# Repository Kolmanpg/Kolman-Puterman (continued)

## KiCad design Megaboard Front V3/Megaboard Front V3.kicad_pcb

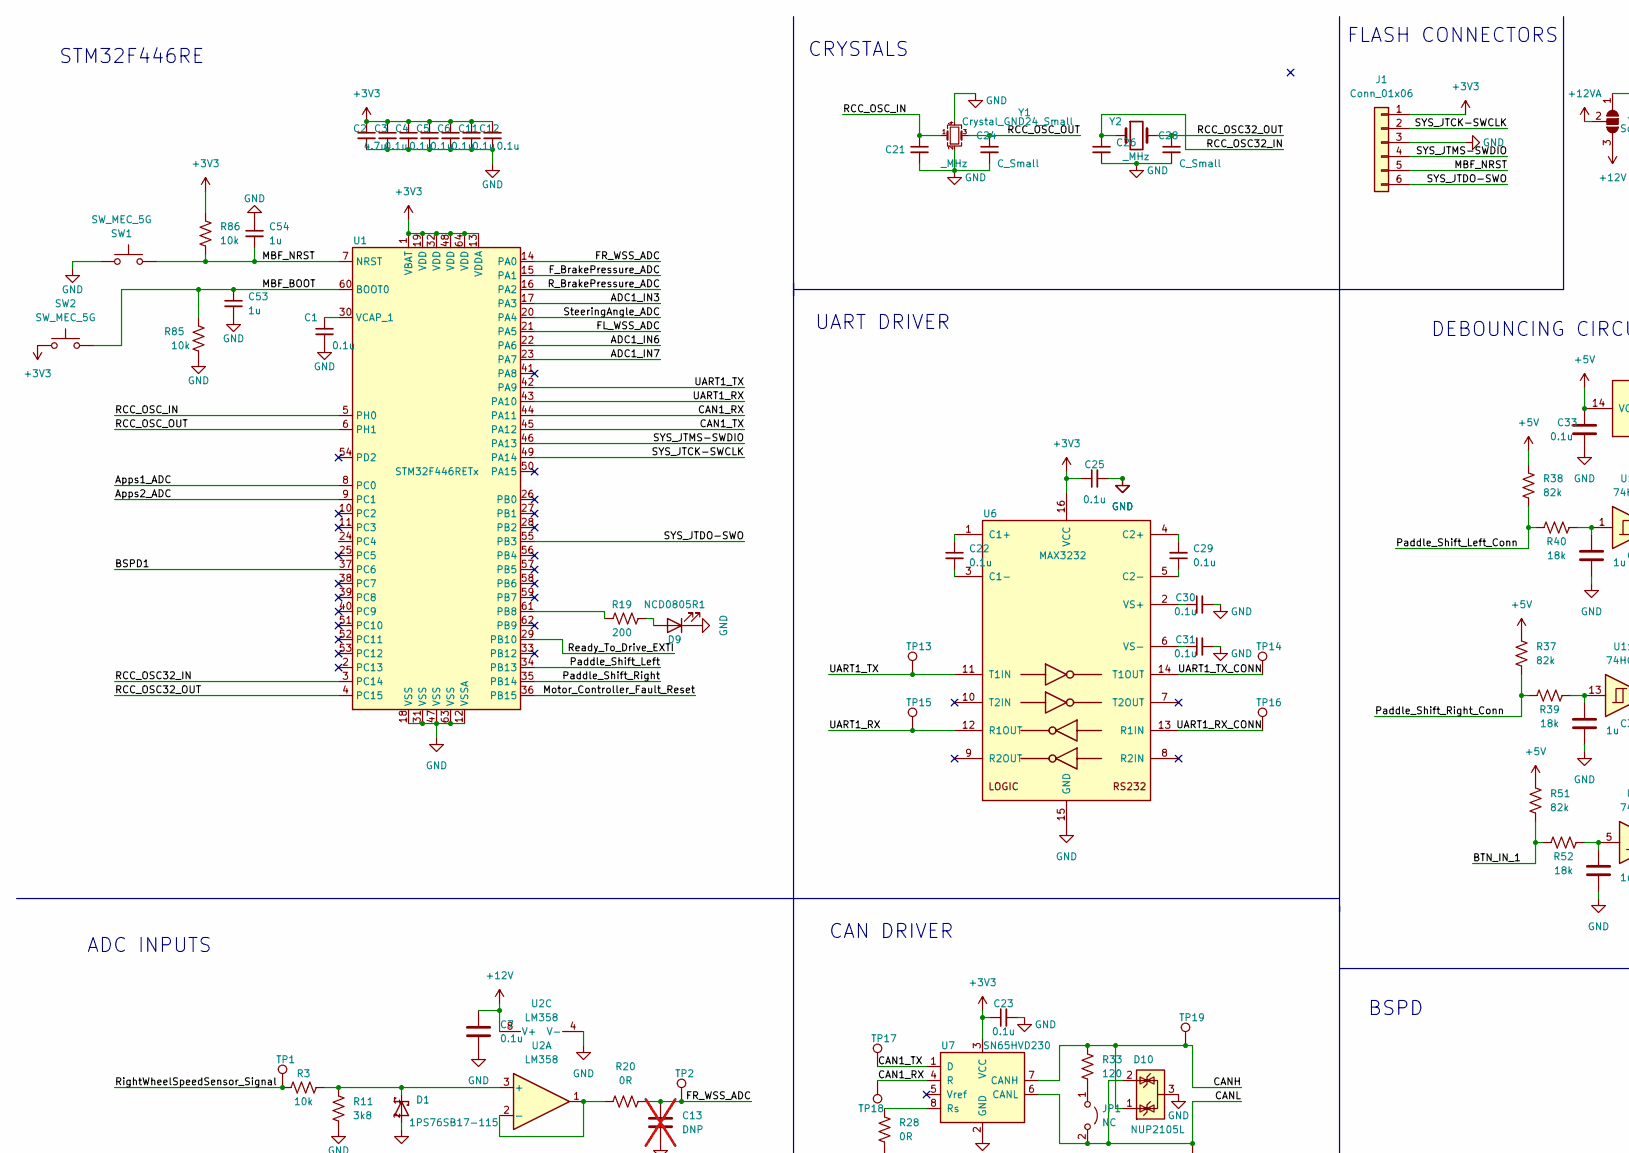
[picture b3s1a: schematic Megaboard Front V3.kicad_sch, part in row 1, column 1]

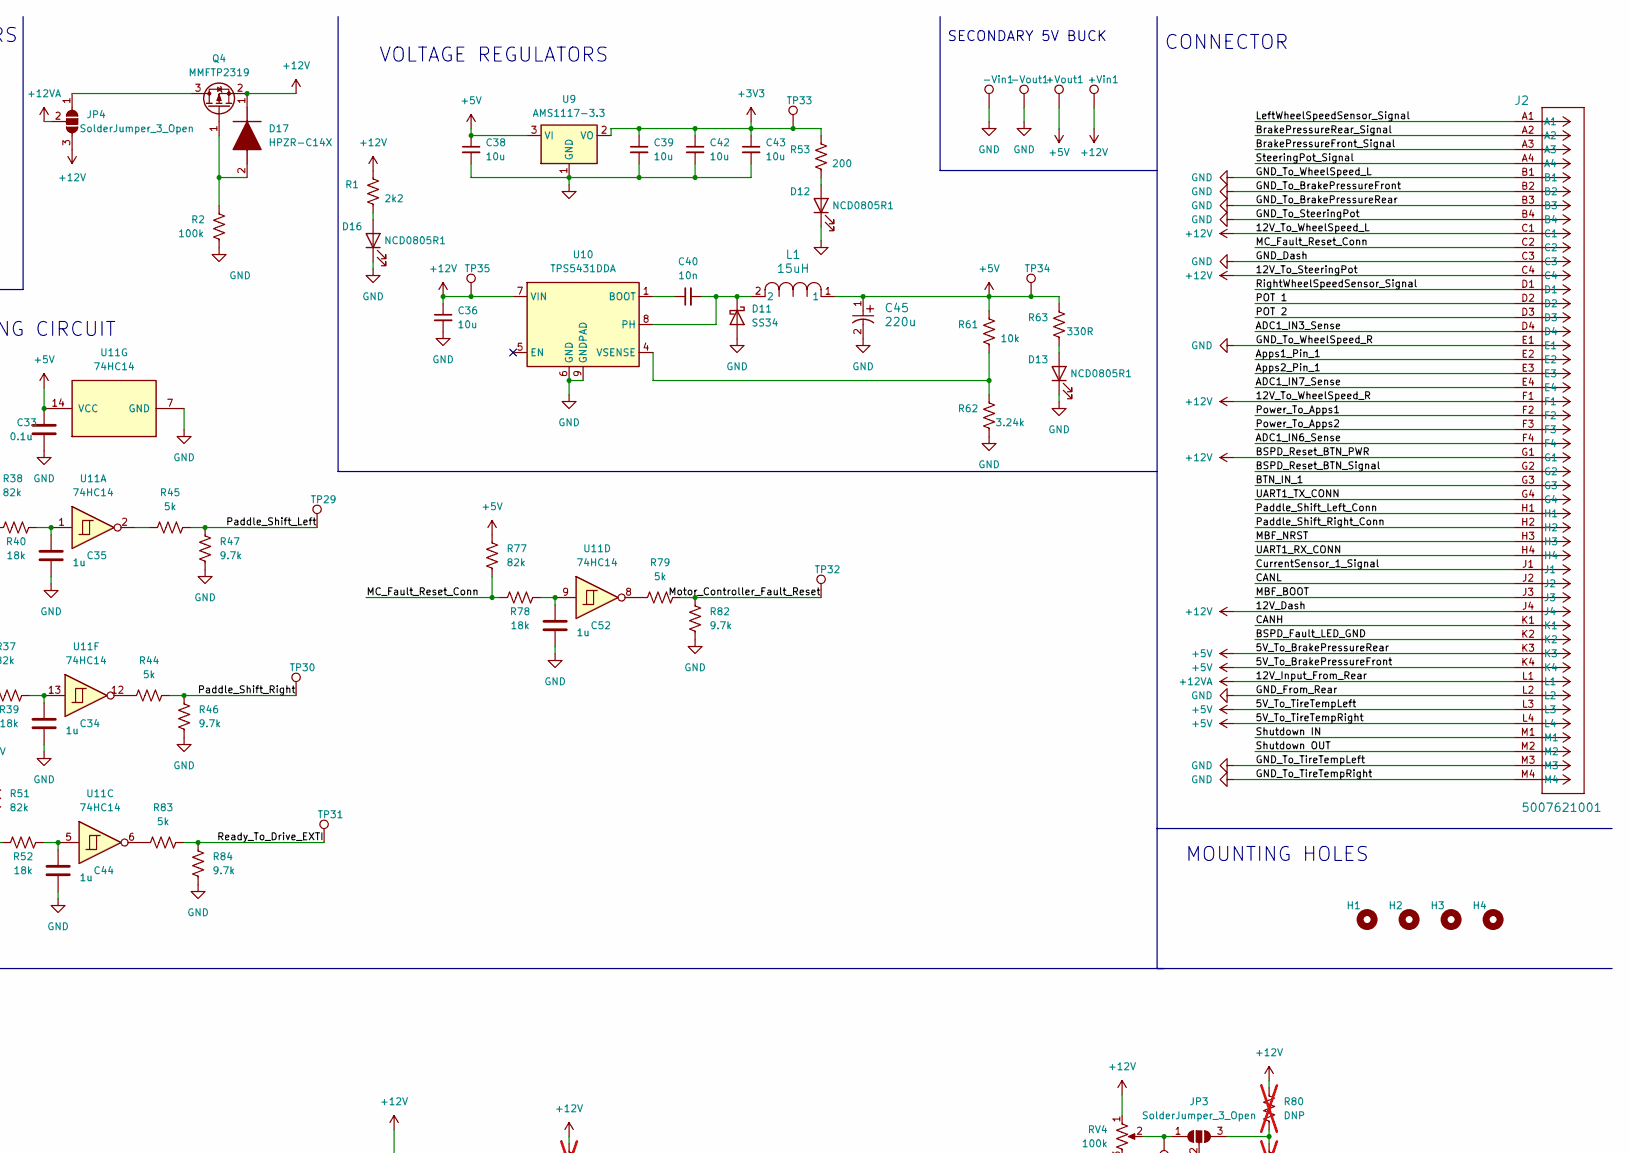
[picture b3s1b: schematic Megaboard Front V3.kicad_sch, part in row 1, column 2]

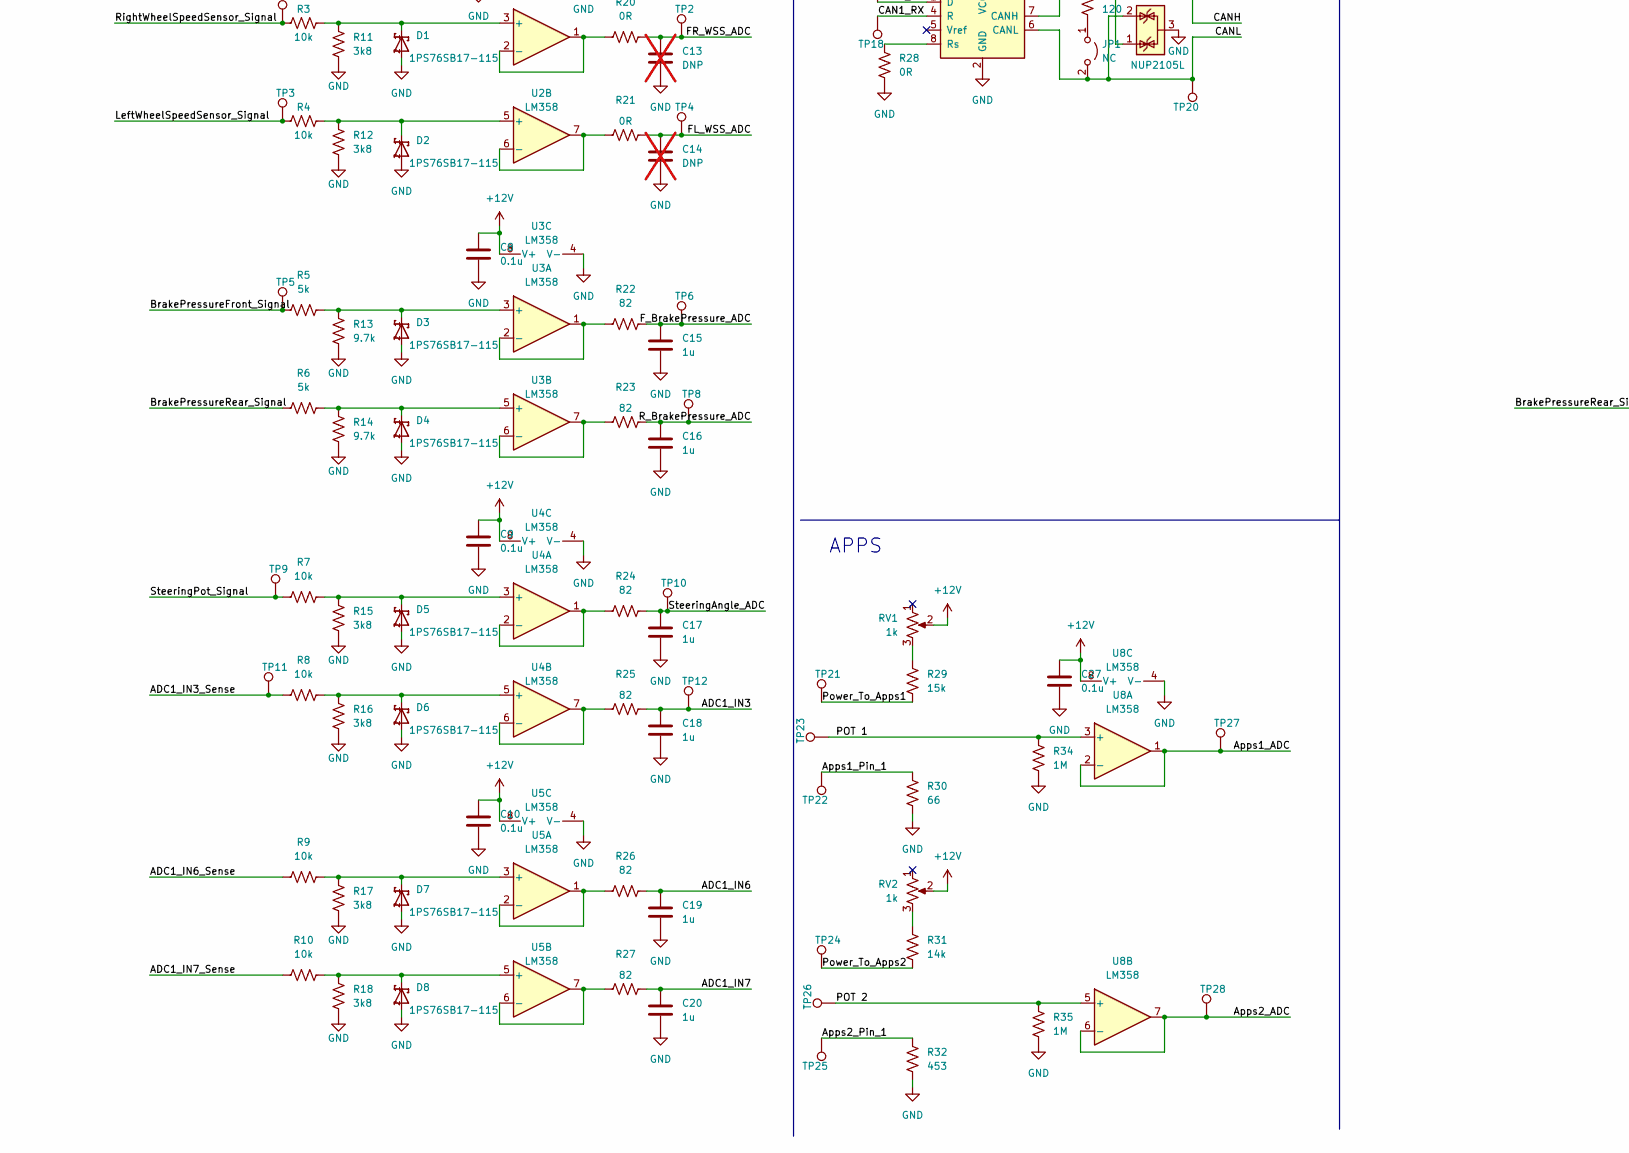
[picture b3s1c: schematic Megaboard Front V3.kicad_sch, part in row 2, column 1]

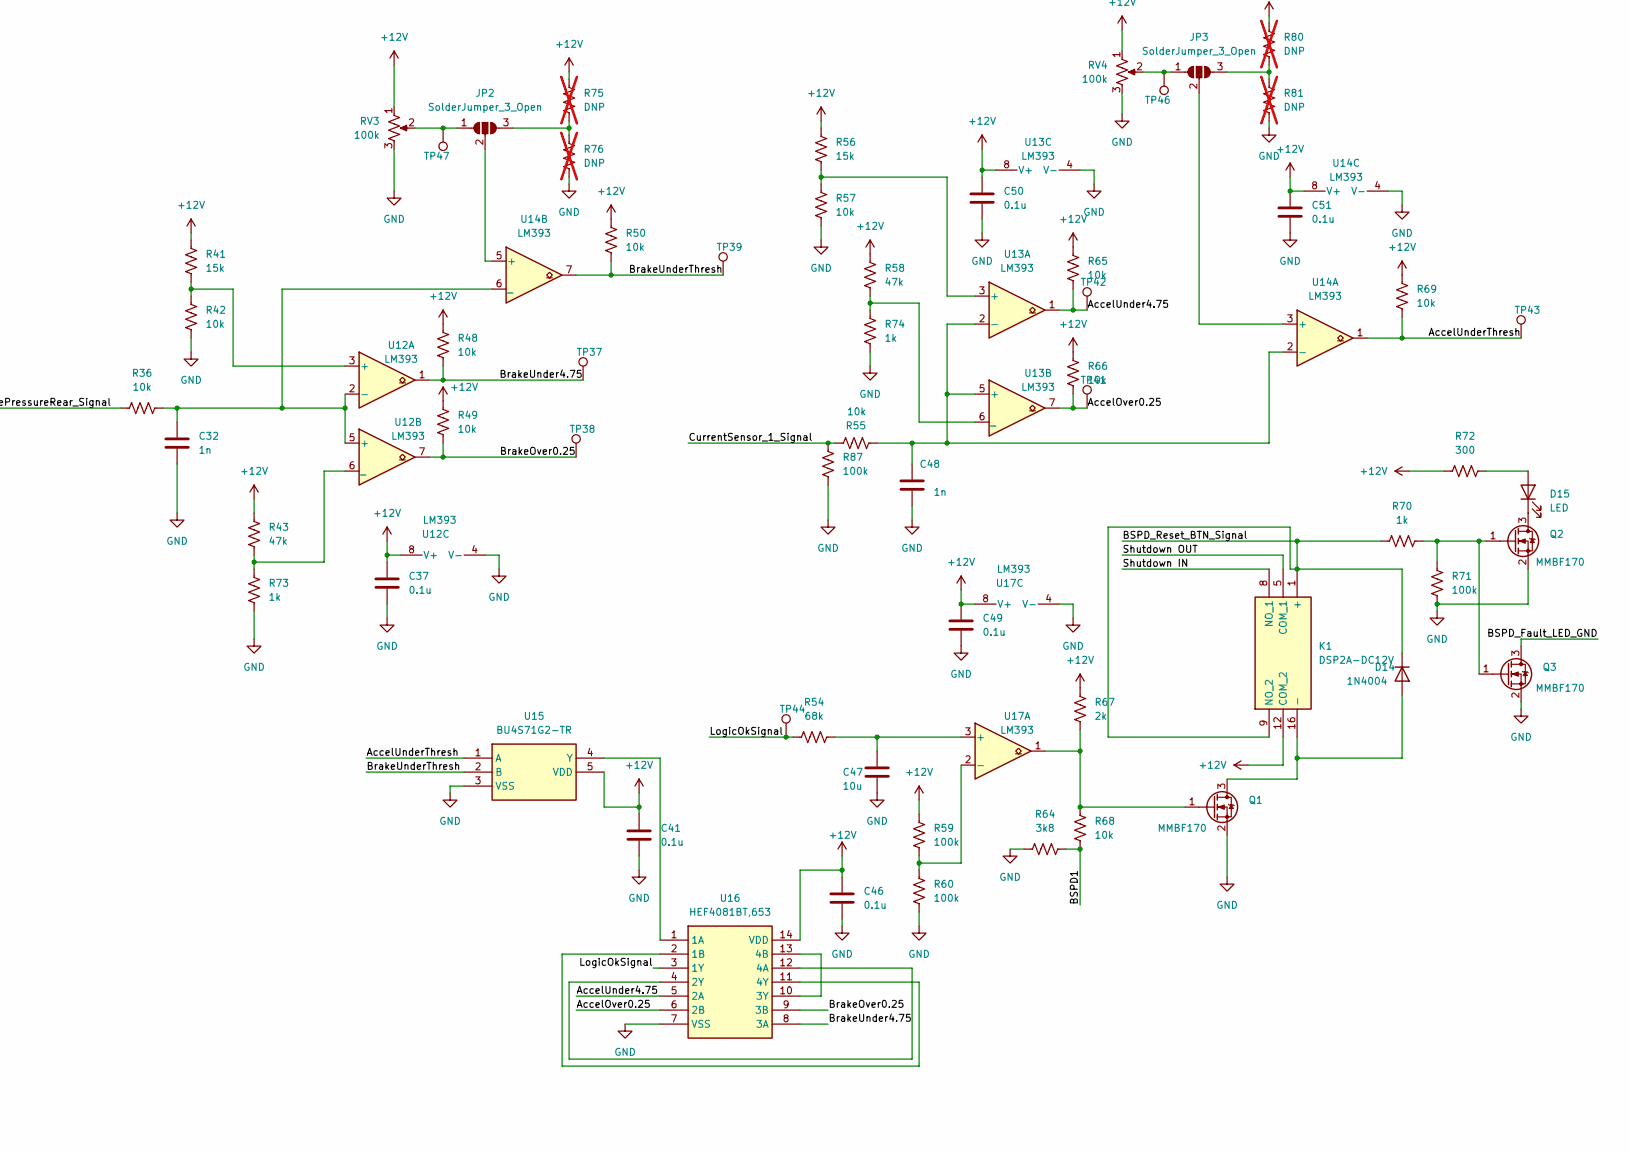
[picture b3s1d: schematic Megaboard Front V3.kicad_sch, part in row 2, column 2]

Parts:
+Vin1: TestPoint_Pad_D1.0mm; MPN DNP; JLCPCB Part # DNP
+Vout1: TestPoint_Pad_D1.0mm; MPN DNP; JLCPCB Part # DNP
-Vin1: TestPoint_Pad_D1.0mm; MPN DNP; JLCPCB Part # DNP
-Vout1: TestPoint_Pad_D1.0mm; MPN DNP; JLCPCB Part # DNP
C1, C3, C4, C5, C6, C11, C12, C22, C23, C25, C29, C30, C31: 0.1u; C_0805_2012Metric_Pad1.18x1.45mm_HandSolder; JLCPCB Part # C49678
C2: 4.7u; C_0805_2012Metric_Pad1.18x1.45mm_HandSolder; JLCPCB Part # C1779
C7, C8, C9, C10, C27, C33: 0.1u; C_0805_2012Metric_Pad1.18x1.45mm_HandSolder; MPN C28233; JLCPCB Part # C49678
C13, C14: DNP; C_0805_2012Metric_Pad1.18x1.45mm_HandSolder; MPN C28323; JLCPCB Part # DNP; not fitted
C15, C16, C17, C18, C19, C20, C34, C35, C44, C52: 1u; C_0805_2012Metric_Pad1.18x1.45mm_HandSolder; MPN C28323; JLCPCB Part # C28323
C21, C26: _MHz; C_0805_2012Metric_Pad1.18x1.45mm_HandSolder; JLCPCB Part # DNP
C24, C28: C_Small; C_0805_2012Metric_Pad1.18x1.45mm_HandSolder; JLCPCB Part # DNP
C32, C48: 1n; C_0805_2012Metric_Pad1.18x1.45mm_HandSolder; MPN C35216; JLCPCB Part # C46653
C36: 10u; C_0805_2012Metric_Pad1.18x1.45mm_HandSolder; MPN C15850; JLCPCB Part # C15850
C37, C41, C46, C49, C50, C51: 0.1u; C_0805_2012Metric_Pad1.18x1.45mm_HandSolder; MPN C35216; JLCPCB Part # C49678
C38, C39, C42, C43: 10u; CP_EIA-3216-18_Kemet-A; MPN C15850; JLCPCB Part # C7171
C40: 10n; C_0805_2012Metric_Pad1.18x1.45mm_HandSolder; MPN C15850; JLCPCB Part # C1710
C45: 220u; PCAP_TPB_D4_PAN; MPN 10TPB220M; JLCPCB Part # C242173
C47: 10u; C_0805_2012Metric_Pad1.18x1.45mm_HandSolder; MPN C13585; JLCPCB Part # C15850
C53, C54: 1u; C_0805_2012Metric_Pad1.18x1.45mm_HandSolder; MPN C15850; JLCPCB Part # C28323
D1, D2, D3, D4, D5, D6, D7, D8: 1PS76SB17-115; SOD323_F_; JLCPCB Part # C551398
D9, D12, D13, D16: NCD0805R1; LED_0805_2012Metric_Pad1.15x1.40mm_HandSolder; MPN C84256; JLCPCB Part # C84256
D10: NUP2105L; SOT-23; JLCPCB Part # C2890118
D11: SS34; D_SMA; JLCPCB Part # C8678
D14: 1N4004; D_SMA_Handsoldering; MPN C95872; JLCPCB Part # C727080
D15: LED; LED_0805_2012Metric_Pad1.15x1.40mm_HandSolder; MPN C2297; JLCPCB Part # C2297
D17: HPZR-C14X; HPZRC14X; Mouser Part Number 771-HPZR-C14X
H1, H2, H3, H4: MountingHole; MountingHole_3.2mm_M3; JLCPCB Part # DNP
J1: Conn_01x06; PinHeader_2x03_P2.54mm_Vertical; JLCPCB Part # DNP
J2: 5007621001; CONN_500762-1001_MOL; JLCPCB Part # DNP
JP1: NC; SolderJumper-2_P1.3mm_Open_RoundedPad1.0x1.5mm; JLCPCB Part # DNP
JP2, JP3, JP4: SolderJumper_3_Open; SolderJumper-3_P1.3mm_Open_RoundedPad1.0x1.5mm
K1: DSP2A-DC12V; RELAY_DSP2A_PAN; Mouser Part Number 769-DSP2A-DC12V
L1: 15uH; IND_CDRH104_SUM; MPN CDRH104RNP-150NC; JLCPCB Part # C225048
Q1, Q2, Q3: MMBF170; SOT-23; MPN C130879; JLCPCB Part # C151058
Q4: MMFTP2319; SOT-23; JLCPCB Part # DNP
R1: 2k2; R_0805_2012Metric_Pad1.20x1.40mm_HandSolder; MPN C17630; JLCPCB Part # C17520
R2: 100k; R_0805_2012Metric_Pad1.20x1.40mm_HandSolder; MPN C17630; JLCPCB Part # C149504
R3, R4, R7, R8, R9, R10: 10k; R_0805_2012Metric_Pad1.20x1.40mm_HandSolder; MPN C23255; JLCPCB Part # C17414
R5, R6, R44, R45, R79, R83: 5k; R_0805_2012Metric_Pad1.20x1.40mm_HandSolder; MPN C23255; JLCPCB Part # C2828700
R11, R12, R15, R16, R17, R18, R64: 3k8; R_0805_2012Metric_Pad1.20x1.40mm_HandSolder; MPN C23255; JLCPCB Part # C228799
R13, R14, R46, R47, R82, R84: 9.7k; R_0805_2012Metric_Pad1.20x1.40mm_HandSolder; MPN C23255; JLCPCB Part # C374689
R19: 200; R_0805_2012Metric_Pad1.20x1.40mm_HandSolder; MPN C706418; JLCPCB Part # C17540
R20, R21: 0R; R_0805_2012Metric_Pad1.20x1.40mm_HandSolder; MPN C23255; JLCPCB Part # C17477
R22, R23, R24, R25, R26, R27: 82; R_0805_2012Metric_Pad1.20x1.40mm_HandSolder; MPN C23255; JLCPCB Part # C17841
R28: 0R; R_0805_2012Metric_Pad1.20x1.40mm_HandSolder; MPN C21189; JLCPCB Part # C17477
R29: 15k; R_0805_2012Metric_Pad1.20x1.40mm_HandSolder; JLCPCB Part # C17475
R30: 66; R_0805_2012Metric_Pad1.20x1.40mm_HandSolder
R31: 14k; R_0805_2012Metric_Pad1.20x1.40mm_HandSolder; JLCPCB Part # C17464
R32: 453; R_0805_2012Metric_Pad1.20x1.40mm_HandSolder
R33: 120; R_0805_2012Metric_Pad1.20x1.40mm_HandSolder; MPN C22787; JLCPCB Part # C17437
R34, R35: 1M; R_0805_2012Metric_Pad1.20x1.40mm_HandSolder; JLCPCB Part # C17514
R36, R48, R49, R50, R55, R65, R66, R69: 10k; R_0805_2012Metric_Pad1.20x1.40mm_HandSolder; MPN C17902; JLCPCB Part # C17414
R37, R38, R51, R77: 82k; R_0805_2012Metric_Pad1.20x1.40mm_HandSolder; MPN C23186; JLCPCB Part # C17840
R39, R40, R52, R78: 18k; R_0805_2012Metric_Pad1.20x1.40mm_HandSolder; MPN C22809; JLCPCB Part # C17506
R41, R56: 15k; R_0805_2012Metric_Pad1.20x1.40mm_HandSolder; MPN C706418; JLCPCB Part # C17475
R42, R57: 10k; R_0805_2012Metric_Pad1.20x1.40mm_HandSolder; MPN C706423; JLCPCB Part # C17414
R43, R58: 47k; R_0805_2012Metric_Pad1.20x1.40mm_HandSolder; MPN C706418; JLCPCB Part # C17713
R53: 200; R_0805_2012Metric_Pad1.20x1.40mm_HandSolder; MPN C17520; JLCPCB Part # C17540
R54: 68k; R_0805_2012Metric_Pad1.20x1.40mm_HandSolder; MPN C73040; JLCPCB Part # C17801
R59, R60, R71, R87: 100k; R_0805_2012Metric_Pad1.20x1.40mm_HandSolder; MPN C17900; JLCPCB Part # C149504
R61: 10k; R_0805_2012Metric_Pad1.20x1.40mm_HandSolder; MPN C17540; JLCPCB Part # C17414
R62: 3.24k; R_0805_2012Metric_Pad1.20x1.40mm_HandSolder; MPN C17540; JLCPCB Part # C4194377
R63: 330R; R_0805_2012Metric_Pad1.20x1.40mm_HandSolder; MPN C17630; JLCPCB Part # C17630
R67: 2k; R_0805_2012Metric_Pad1.20x1.40mm_HandSolder; MPN C4410; JLCPCB Part # C17604
R68: 10k; R_0805_2012Metric_Pad1.20x1.40mm_HandSolder; MPN C4410; JLCPCB Part # C17414
R70: 1k; R_0805_2012Metric_Pad1.20x1.40mm_HandSolder; MPN C4410; JLCPCB Part # C17513
R72: 300; R_0805_2012Metric_Pad1.20x1.40mm_HandSolder; MPN C17909; JLCPCB Part # C17617
R73, R74: 1k; R_0805_2012Metric_Pad1.20x1.40mm_HandSolder; MPN C706423; JLCPCB Part # C17513
R75, R76, R80, R81: DNP; R_0805_2012Metric_Pad1.20x1.40mm_HandSolder; MPN C706418; JLCPCB Part # C865361; not fitted
R85, R86: 10k; R_0805_2012Metric_Pad1.20x1.40mm_HandSolder; MPN C17414; JLCPCB Part # C17414
RV1, RV2: 1k; Potentiometer_Bourns_3296W_Vertical; MPN C83686
RV3, RV4: 100k; Potentiometer_Bourns_3296W_Vertical; MPN C83686
SW1: SW_MEC_5G; SW_Push_1P1T_XKB_TS-1187A; MPN C318884; JLCPCB Part # C318884
SW2: SW_MEC_5G; SW_Push_1P1T_XKB_TS-1187A; JLCPCB Part # C318884
TP1, TP2, TP3, TP4, TP5, TP6, TP8, TP9, TP10, TP11, TP12, TP13, TP14, TP15, TP16, TP17, TP18, TP19, TP20, TP21, TP22, TP23, TP24, TP25, TP26, TP27, TP28, TP29, TP30, TP31, TP32, TP33, TP34, TP35, TP37, TP38, TP39, TP41, TP42, TP43, TP44, TP46, TP47: TestPoint_Pad_D1.0mm; MPN DNP; JLCPCB Part # DNP
U1: STM32F446RETx; LQFP-64_10x10mm_P0.5mm; JLCPCB Part # C69336
U2, U3, U4, U5, U8: LM358; SOIC-8_3.9x4.9mm_P1.27mm; MPN C7950; JLCPCB Part # C9418
U6: MAX3232; SOIC-16_3.9x9.9mm_P1.27mm; JLCPCB Part # C18261
U7: SN65HVD230; SOIC-8_3.9x4.9mm_P1.27mm; MPN C12084; JLCPCB Part # C12084
U9: AMS1117-3.3; SOT-223-3_TabPin2; JLCPCB Part # C6186
U10: TPS5431DDA; TI_SO-PowerPAD-8_ThermalVias; JLCPCB Part # C9864
U11: 74HC14; SOIC-14_3.9x8.7mm_P1.27mm; MPN C5605; JLCPCB Part # C5605
U12, U13, U14, U17: LM393; SOIC-8_3.9x4.9mm_P1.27mm; MPN C7955; JLCPCB Part # C32901
U15: BU4S71G2-TR; SOT95P280X125-5N; Mouser Part Number 755-BU4S71G2-TR
U16: HEF4081BT,653; SOIC127P600X175-14N; Mouser Part Number 771-HEF4081BTD-T
Y1: Crystal_GND24_Small; Crystal_SMD_3225-4Pin_3.2x2.5mm_HandSoldering
Y2: Crystal_GND23_Small; Crystal_SMD_3215-2Pin_3.2x1.5mm; JLCPCB Part # DNP

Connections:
+3V3: C2.1, C3.1, C4.1, C5.1, C6.1, C11.1, C12.1, C23.1, C25.1, C39.1, C42.1, C43.1, J1.1, R53.1, R86.1, SW2.1 (A), TP33.1, U1.1 (VBAT), U1.13 (VDDA), U1.19 (VDD), U1.32 (VDD), U1.48 (VDD), U1.64 (VDD), U6.16 (VCC), U7.3 (VCC), U9.2 (VO)
+5V: +Vout1.1, C33.1, C38.1, C45.1, J2.K3, J2.K4, J2.L3, J2.L4, L1.1, R37.1, R38.1, R51.1, R61.1, R63.1, R77.1, TP34.1, U9.3 (VI), U11.14 (VCC)
+12V: +Vin1.1, C7.1, C8.1, C9.1, C10.1, C27.1, C36.1, C37.1, C41.1, C46.1, C49.1, C50.1, C51.1, D17.1 (K), J2.C1, J2.C4, J2.F1, J2.G1, J2.J4, JP4.3 (B), K1.12 (COM_2), Q4.2 (S), R1.1, R41.1, R43.1, R48.1, R49.1, R50.1, R56.1, R58.1, R59.1, R65.1, R66.1, R67.1, R69.1, R72.1, R75.1, R80.1, RV1.2, RV2.2, RV3.1, RV4.1, TP35.1, U2.8 (V+), U3.8 (V+), U4.8 (V+), U5.8 (V+), U8.8 (V+), U10.7 (VIN), U12.8 (V+), U13.8 (V+), U14.8 (V+), U15.5 (VDD), U16.14 (VDD), U17.8 (V+)
+12VA: J2.L1, JP4.2 (C)
/ADC1_IN3: C18.1, R25.2, TP12.1, U1.17 (PA3)
/ADC1_IN3_Sense: J2.D4, R8.1, TP11.1
/ADC1_IN6: C19.1, R26.2, U1.22 (PA6)
/ADC1_IN6_Sense: J2.F4, R9.1
/ADC1_IN7: C20.1, R27.2, U1.23 (PA7)
/ADC1_IN7_Sense: J2.E4, R10.1
/AccelOver0.25: R66.2, TP41.1, U13.7, U16.6 (2B)
/AccelUnder4.75: R65.2, TP42.1, U13.1, U16.5 (2A)
/AccelUnderThresh: R69.2, TP43.1, U14.1, U15.1 (A)
/Apps1_ADC: TP27.1, U1.8 (PC0), U8.1, U8.2 (-)
/Apps1_Pin_1: J2.E2, R30.2, TP22.1
/Apps2_ADC: TP28.1, U1.9 (PC1), U8.6 (-), U8.7
/Apps2_Pin_1: J2.E3, R32.2, TP25.1
/BSPD1: R64.2, R68.2, U1.37 (PC6)
/BSPD_Fault_LED_GND: J2.K2, Q3.3 (D)
/BSPD_Reset_BTN_Signal: D14.1 (K), J2.G2, K1.1 (+), K1.9 (NO_2), R70.1
/BTN_IN_1: J2.G3, R51.2, R52.1
/BrakeOver0.25: R49.2, TP38.1, U12.7, U16.9 (3B)
/BrakePressureFront_Signal: J2.A3, R5.1, TP5.1
/BrakePressureRear_Signal: J2.A2, R6.1, R36.1
/BrakeUnder4.75: R48.2, TP37.1, U12.1, U16.8 (3A)
/BrakeUnderThresh: R50.2, TP39.1, U14.7, U15.2 (B)
/CAN1_RX: TP18.1, U1.44 (PA11), U7.4 (R)
/CAN1_TX: TP17.1, U1.45 (PA12), U7.1 (D)
/CANH: D10.1 (K), J2.K1, R33.2, TP19.1, U7.7 (CANH)
/CANL: D10.2 (K), J2.J2, JP1.2 (B), TP20.1, U7.6 (CANL)
/CurrentSensor_1_Signal: J2.J1, R55.1, R87.1
/FL_WSS_ADC: C14.1, R21.2, TP4.1, U1.21 (PA5)
/FR_WSS_ADC: C13.1, R20.2, TP2.1, U1.14 (PA0)
/F_BrakePressure_ADC: C15.1, R22.2, TP6.1, U1.15 (PA1)
/LeftWheelSpeedSensor_Signal: J2.A1, R4.1, TP3.1
/LogicOkSignal: R54.1, TP44.1, U16.3 (1Y)
/MBF_BOOT: C53.1, J2.J3, R85.1, SW2.2 (B), U1.60 (BOOT0)
/MBF_NRST: C54.2, J1.5, J2.H3, R86.2, SW1.2 (B), U1.7 (NRST)
/MC_Fault_Reset_Conn: J2.C2, R77.2, R78.1
/Motor_Controller_Fault_Reset: R79.2, R82.2, TP32.1, U1.36 (PB15)
/POT 1: J2.D2, R34.1, TP23.1, U8.3 (+)
/POT 2: J2.D3, R35.1, TP26.1, U8.5 (+)
/Paddle_Shift_Left: R45.2, R47.2, TP29.1, U1.34 (PB13)
/Paddle_Shift_Left_Conn: J2.H1, R38.2, R40.1
/Paddle_Shift_Right: R44.2, R46.2, TP30.1, U1.35 (PB14)
/Paddle_Shift_Right_Conn: J2.H2, R37.2, R39.1
/Power_To_Apps1: J2.F2, R29.2, TP21.1
/Power_To_Apps2: J2.F3, R31.2, TP24.1
/RCC_OSC32_IN: C26.1, U1.3 (PC14), Y2.1
/RCC_OSC32_OUT: C28.1, U1.4 (PC15), Y2.2
/RCC_OSC_IN: C21.1, U1.5 (PH0), Y1.1
/RCC_OSC_OUT: C24.1, U1.6 (PH1), Y1.3
/R_BrakePressure_ADC: C16.1, R23.2, TP8.1, U1.16 (PA2)
/Ready_To_Drive_EXTI: R83.2, R84.2, TP31.1, U1.29 (PB10)
/RightWheelSpeedSensor_Signal: J2.D1, R3.1, TP1.1
/SYS_JTCK-SWCLK: J1.2, U1.49 (PA14)
/SYS_JTDO-SWO: J1.6, U1.55 (PB3)
/SYS_JTMS-SWDIO: J1.4, U1.46 (PA13)
/Shutdown IN: J2.M1, K1.8 (NO_1)
/Shutdown OUT: J2.M2, K1.5 (COM_1)
/SteeringAngle_ADC: C17.1, R24.2, TP10.1, U1.20 (PA4)
/SteeringPot_Signal: J2.A4, R7.1, TP9.1
/UART1_RX: TP15.1, U1.43 (PA10), U6.12 (R1OUT)
/UART1_RX_CONN: J2.H4, TP16.1, U6.13 (R1IN)
/UART1_TX: TP13.1, U1.42 (PA9), U6.11 (T1IN)
/UART1_TX_CONN: J2.G4, TP14.1, U6.14 (T1OUT)
GND: -Vin1.1, -Vout1.1, C1.2, C2.2, C3.2, C4.2, C5.2, C6.2, C7.2, C8.2, C9.2, C10.2, C11.2, C12.2, C13.2, C14.2, C15.2, C16.2, C17.2, C18.2, C19.2, C20.2, C21.2, C23.2, C24.2, C25.2, C26.2, C27.2, C28.2, C30.2, C31.2, C32.2, C33.2, C34.2, C35.2, C36.2, C37.2, C38.2, C39.2, C41.2, C42.2, C43.2, C44.2, C45.2, C46.2, C47.2, C48.2, C49.2, C50.2, C51.2, C52.2, C53.2, C54.1, D1.2, D2.2, D3.2, D4.2, D5.2, D6.2, D7.2, D8.2, D9.1 (K), D10.3 (A), D11.2 (A), D12.1 (K), D13.1 (K), D16.1 (K), J1.3, J2.B1, J2.B2, J2.B3, J2.B4, J2.C3, J2.E1, J2.L2, J2.M3, J2.M4, Q1.2 (S), Q2.2 (S), Q3.2 (S), R2.2, R11.1, R12.1, R13.1, R14.1, R15.1, R16.1, R17.1, R18.1, R28.2, R30.1, R32.1, R34.2, R35.2, R42.2, R46.1, R47.1, R57.2, R60.2, R62.2, R64.1, R71.1, R73.2, R74.2, R76.2, R81.2, R82.1, R84.1, R85.2, R87.2, RV3.3, RV4.3, SW1.1 (A), U1.12 (VSSA), U1.18 (VSS), U1.31 (VSS), U1.47 (VSS), U1.63 (VSS), U2.4 (V-), U3.4 (V-), U4.4 (V-), U5.4 (V-), U6.15 (GND), U7.2 (GND), U8.4 (V-), U9.1 (GND), U10.6 (GND), U10.9 (GNDPAD), U11.7 (GND), U12.4 (V-), U13.4 (V-), U14.4 (V-), U15.3 (VSS), U16.7 (VSS), U17.4 (V-), Y1.2, Y1.4
unnamed: C34.1, R39.2, U11.13
unnamed: C35.1, R40.2, U11.1
unnamed: C44.1, R52.2, U11.5
unnamed: C52.1, R78.2, U11.9
unnamed: D9.2 (A), R19.1
unnamed: C40.2, D11.1 (K), L1.2, U10.8 (PH)
unnamed: D12.2 (A), R53.2
unnamed: D13.2 (A), R63.2
unnamed: D14.2 (A), K1.16 (-), Q1.3 (D)
unnamed: D15.2 (A), R72.2
unnamed: D15.1 (K), Q2.3 (D)
unnamed: D16.2 (A), R1.2
unnamed: D17.2 (A), Q4.1 (G), R2.1
unnamed: JP1.1 (A), R33.1
unnamed: JP2.1 (A), RV3.2, TP47.1
unnamed: JP2.3 (B), R75.2, R76.1
unnamed: JP2.2 (C), U14.5 (+)
unnamed: JP3.1 (A), RV4.2, TP46.1
unnamed: JP3.3 (B), R80.2, R81.1
unnamed: JP3.2 (C), U14.3 (+)
unnamed: JP4.1 (A), Q4.3 (D)
unnamed: Q1.1 (G), R67.2, R68.1, U17.1
unnamed: Q2.1 (G), Q3.1 (G), R70.2, R71.2
unnamed: R29.1, RV1.3
unnamed: R31.1, RV2.3
unnamed: R44.1, U11.12
unnamed: R45.1, U11.2
unnamed: R79.1, U11.8
unnamed: R83.1, U11.6
unnamed: R19.2, U1.61 (PB8)
unnamed: C1.1, U1.30 (VCAP_1)
unnamed: D1.1, R3.2, R11.2, U2.3 (+)
unnamed: R20.1, U2.1, U2.2 (-)
unnamed: D2.1, R4.2, R12.2, U2.5 (+)
unnamed: R21.1, U2.6 (-), U2.7
unnamed: D3.1, R5.2, R13.2, U3.3 (+)
unnamed: R22.1, U3.1, U3.2 (-)
unnamed: D4.1, R6.2, R14.2, U3.5 (+)
unnamed: R23.1, U3.6 (-), U3.7
unnamed: D5.1, R7.2, R15.2, U4.3 (+)
unnamed: R24.1, U4.1, U4.2 (-)
unnamed: D6.1, R8.2, R16.2, U4.5 (+)
unnamed: R25.1, U4.6 (-), U4.7
unnamed: D7.1, R9.2, R17.2, U5.3 (+)
unnamed: R26.1, U5.1, U5.2 (-)
unnamed: D8.1, R10.2, R18.2, U5.5 (+)
unnamed: R27.1, U5.6 (-), U5.7
unnamed: C22.1, U6.1 (C1+)
unnamed: C22.2, U6.3 (C1-)
unnamed: C29.2, U6.4 (C2+)
unnamed: C29.1, U6.5 (C2-)
unnamed: C30.1, U6.2 (VS+)
unnamed: C31.1, U6.6 (VS-)
unnamed: R28.1, U7.8 (Rs)
unnamed: C40.1, U10.1 (BOOT)
unnamed: R61.2, R62.1, U10.4 (VSENSE)
unnamed: R41.2, R42.1, U12.3 (+)
unnamed: C32.1, R36.2, U12.2 (-), U12.5 (+), U14.6 (_)
unnamed: R43.2, R73.1, U12.6 (_)
unnamed: R56.2, R57.1, U13.3 (+)
unnamed: C48.1, R55.2, U13.2 (-), U13.5 (+), U14.2 (-)
unnamed: R58.2, R74.1, U13.6 (_)
unnamed: U15.4 (Y), U16.1 (1A)
unnamed: U16.2 (1B), U16.11 (4Y)
unnamed: U16.4 (2Y), U16.12 (4A)
unnamed: U16.10 (3Y), U16.13 (4B)
unnamed: C47.1, R54.2, U17.3 (+)
unnamed: R59.2, R60.1, U17.2 (-)

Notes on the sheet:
MOUNTING HOLES
UART DRIVER
CAN DRIVER
VOLTAGE REGULATORS
BSPD
STM32F446RE
FLASH CONNECTORS
CRYSTALS
SECONDARY 5V BUCK
DEBOUNCING CIRCUIT
APPS
ADC INPUTS
CONNECTOR

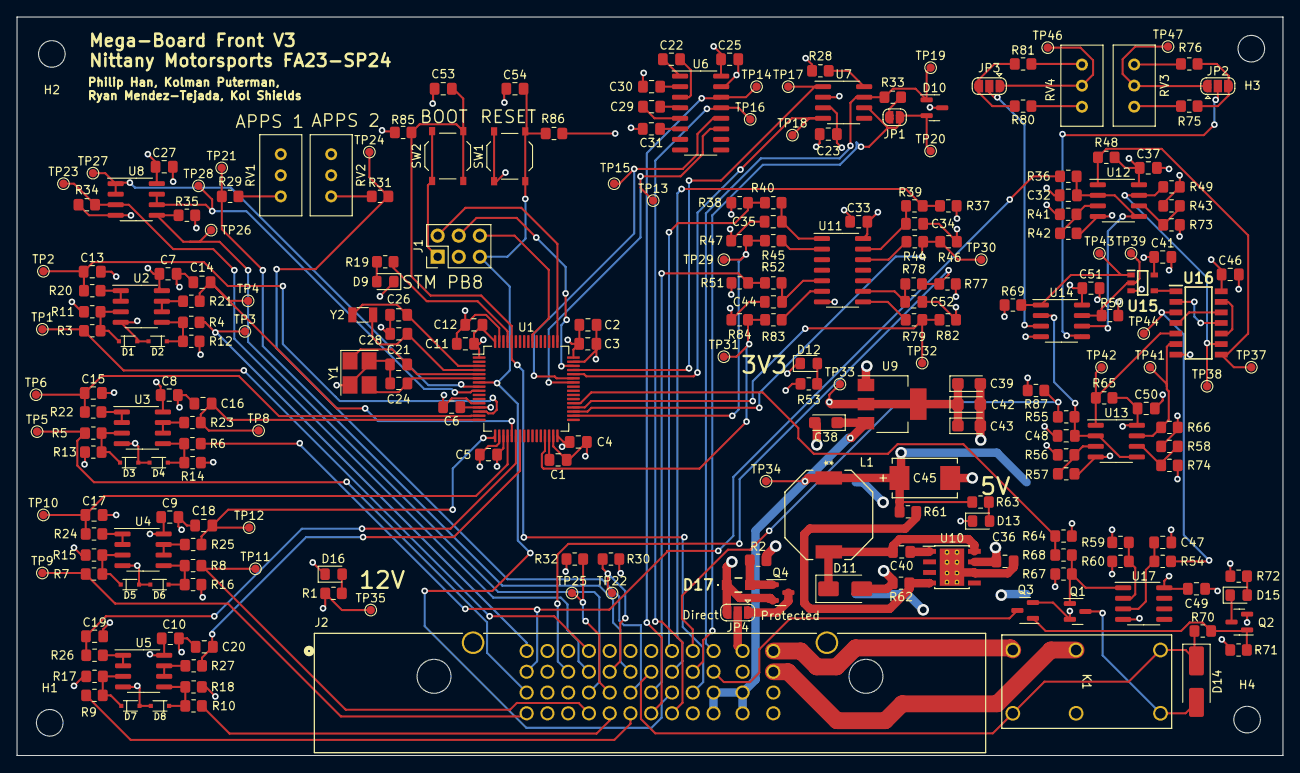
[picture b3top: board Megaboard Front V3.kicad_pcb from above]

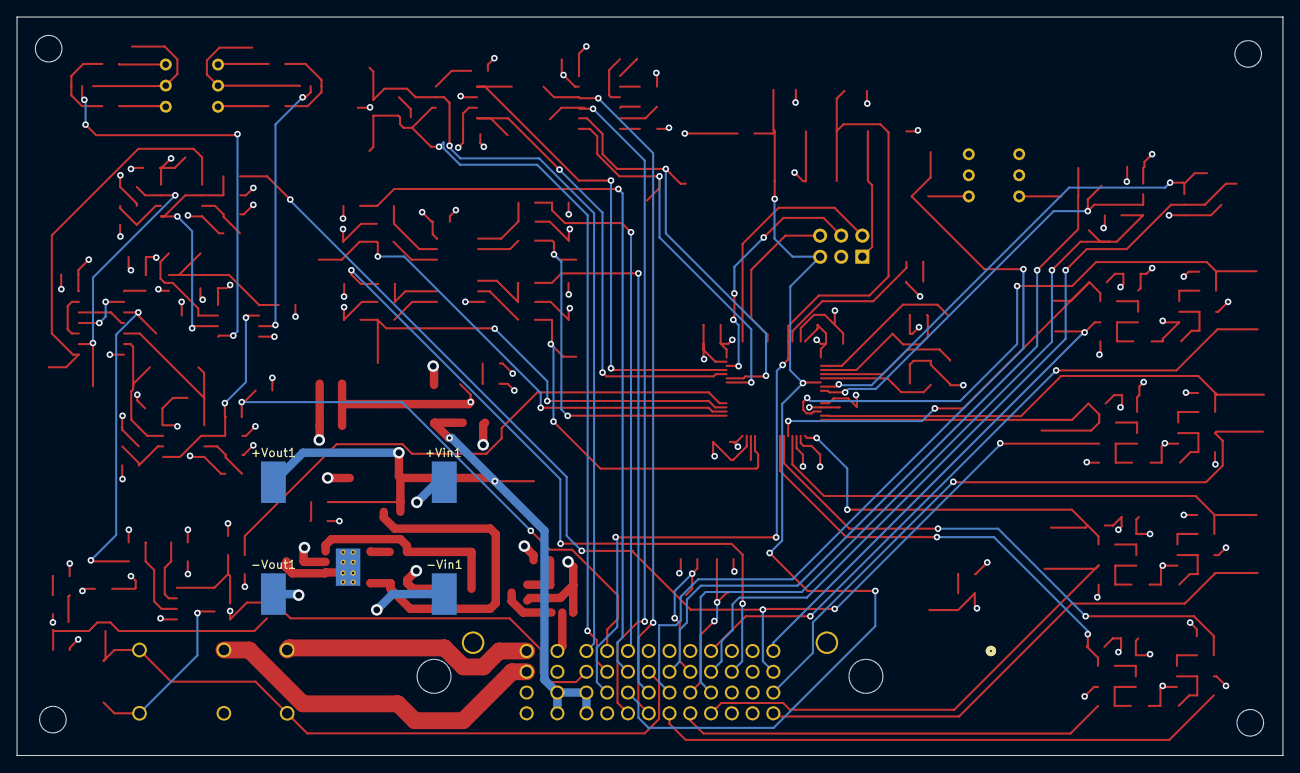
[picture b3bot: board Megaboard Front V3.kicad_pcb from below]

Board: 4 copper layers, 152.4 x 88.9 mm, 246 parts (4 on the bottom side), 135 nets.

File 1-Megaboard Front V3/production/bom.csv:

Designator,Footprint,Quantity,Value,LCSC Part #
"+VIN1, +VOUT1, -VIN1, -VOUT1, TP1, TP10, TP11, TP12, TP13, TP14, TP15, TP16, TP17, TP18, TP19, TP2, TP20, TP21, TP22, TP23, TP24, TP25, TP26, TP27, TP28, TP29, TP3, TP30, TP31, TP32, TP33, TP34, TP35, TP37, TP38, TP39, TP4, TP41, TP42, TP43, TP44, TP46, TP47, TP5, TP6, TP8, TP9",TestPoint_Pad_D1.0mm,47,~,DNP
"C1, C10, C11, C12, C22, C23, C25, C27, C29, C3, C30, C31, C33, C37, C4, C41, C46, C49, C5, C50, C51, C6, C7, C8, C9",0805,25,0.1u,C49678
"C13, C14",0805,2,DNP,DNP
"C15, C16, C17, C18, C19, C20, C34, C35, C44, C52, C53, C54",0805,12,1u,C28323
C2,0805,1,4.7u,C1779
"C21, C26",0805,2,_MHz,DNP
"C24, C28",0805,2,C_Small,DNP
"C32, C48",0805,2,1n,C46653
"C36, C47",0805,2,10u,C15850
"C38, C39, C42, C43",CP_EIA-3216-18_Kemet-A,4,10u,C7171
C40,0805,1,10n,C1710
C45,PCAP_TPB_D4_PAN,1,220u,C242173
"D1, D2, D3, D4, D5, D6, D7, D8",SOD323_F_,8,1PS76SB17-115,C551398
D10,SOT-23,1,NUP2105L,C2890118
D11,D_SMA,1,SS34,C8678
"D12, D13, D16, D9",0805,4,NCD0805R1,C84256
D14,D_SMA_Handsoldering,1,1N4004,C727080
D15,0805,1,LED,C2297
D17,HPZRC14X,1,HPZR-C14X,DNP
"H1, H2, H3, H4",MountingHole_3.2mm_M3,4,MountingHole,DNP
J1,PinHeader_2x03_P2.54mm_Vertical,1,Conn_01x06,DNP
J2,CONN_500762-1001_MOL,1,5007621001,DNP
JP1,SolderJumper-2_P1.3mm_Open_RoundedPad1.0x1.5mm,1,NC,DNP
"JP2, JP3, JP4",SolderJumper-3_P1.3mm_Open_RoundedPad1.0x1.5mm,3,SolderJumper_3_Open,
K1,RELAY_DSP2A_PAN,1,DSP2A-DC12V,DNP
L1,IND_CDRH104_SUM,1,15uH,C225048
"Q1, Q2, Q3",SOT-23,3,MMBF170,C151058
Q4,SOT-23,1,MMFTP2319,DNP
R1,0805,1,2k2,C17520
"R10, R3, R36, R4, R42, R48, R49, R50, R55, R57, R61, R65, R66, R68, R69, R7, R8, R85, R86, R9",0805,20,10k,C17414
"R11, R12, R15, R16, R17, R18, R64",0805,7,3k8,C228799
"R13, R14, R46, R47, R82, R84",0805,6,9.7k,C374689
"R19, R53",0805,2,200,C17540
"R2, R59, R60, R71, R87",0805,5,100k,C149504
"R20, R21, R28",0805,3,0R,C17477
"R22, R23, R24, R25, R26, R27",0805,6,82,C17841
"R29, R41, R56",0805,3,15k,C17475
R30,0805,1,66,
R31,0805,1,14k,C17464
R32,0805,1,453,
R33,0805,1,120,C17437
"R34, R35",0805,2,1M,C17514
"R37, R38, R51, R77",0805,4,82k,C17840
"R39, R40, R52, R78",0805,4,18k,C17506
"R43, R58",0805,2,47k,C17713
"R44, R45, R5, R6, R79, R83",0805,6,5k,C2828700
R54,0805,1,68k,C17801
R62,0805,1,3.24k,C4194377
R63,0805,1,330R,C17630
R67,0805,1,2k,C17604
"R70, R73, R74",0805,3,1k,C17513
R72,0805,1,300,C17617
"R75, R76, R80, R81",0805,4,DNP,C865361
"RV1, RV2",Potentiometer_Bourns_3296W_Vertical,2,1k,
"RV3, RV4",Potentiometer_Bourns_3296W_Vertical,2,100k,
"SW1, SW2",SW_Push_1P1T_XKB_TS-1187A,2,SW_MEC_5G,C318884
U1,LQFP-64_10x10mm_P0.5mm,1,STM32F446RETx,C69336
U10,TI_SO-PowerPAD-8_ThermalVias,1,TPS5431DDA,C9864
U11,SOIC-14_3.9x8.7mm_P1.27mm,1,74HC14,C5605
"U12, U13, U14, U17",SOIC-8_3.9x4.9mm_P1.27mm,4,LM393,C32901
U15,SOT95P280X125-5N,1,BU4S71G2-TR,C2837802
U16,SOIC127P600X175-14N,1,"HEF4081BT,653",C148318
"U2, U3, U4, U5, U8",SOIC-8_3.9x4.9mm_P1.27mm,5,LM358,C9418
U6,SOIC-16_3.9x9.9mm_P1.27mm,1,MAX3232,C18261
U7,SOIC-8_3.9x4.9mm_P1.27mm,1,SN65HVD230,C12084
U9,SOT-223-3_TabPin2,1,AMS1117-3.3,C6186
Y1,Crystal_SMD_3225-4Pin_3.2x2.5mm_HandSoldering,1,Crystal_GND24_Small,
Y2,Crystal_SMD_3215-2Pin_3.2x1.5mm,1,Crystal_GND23_Small,DNP

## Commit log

2024-11-19 Restructured all Folders
2024-11-19 Updated .gitignore
2024-11-19 Updated gitignore
2024-11-19 Reworked Folder Organization
